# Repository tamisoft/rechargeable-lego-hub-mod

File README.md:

# LEGO HUB-mod, rechargable battery

## Project
The Project was created using KiCAD 5.1.5.
Should be manufactured on a <0.8mm thick PCB (eg. oshpark's 2oz copper service).
The "production" directory has an "interactive bom" to assist with the hand assembly.

## Features
- USB charging at about 400mA
- TI BQ25886, 2A boost charger, optimized for 2S Li-Ion
- NTC
- connector for an 8.4V battery

Recommended battery:
[Soshine 9V 650mAh 6F22](https://lygte-info.dk/review/batteries9V/Soshine%209V%20LiIon%20650mAh%20(White)%20UK.html)

## Finished build
### Board assembled

### USB input

### Charging indicators
- red: charging
- green: power

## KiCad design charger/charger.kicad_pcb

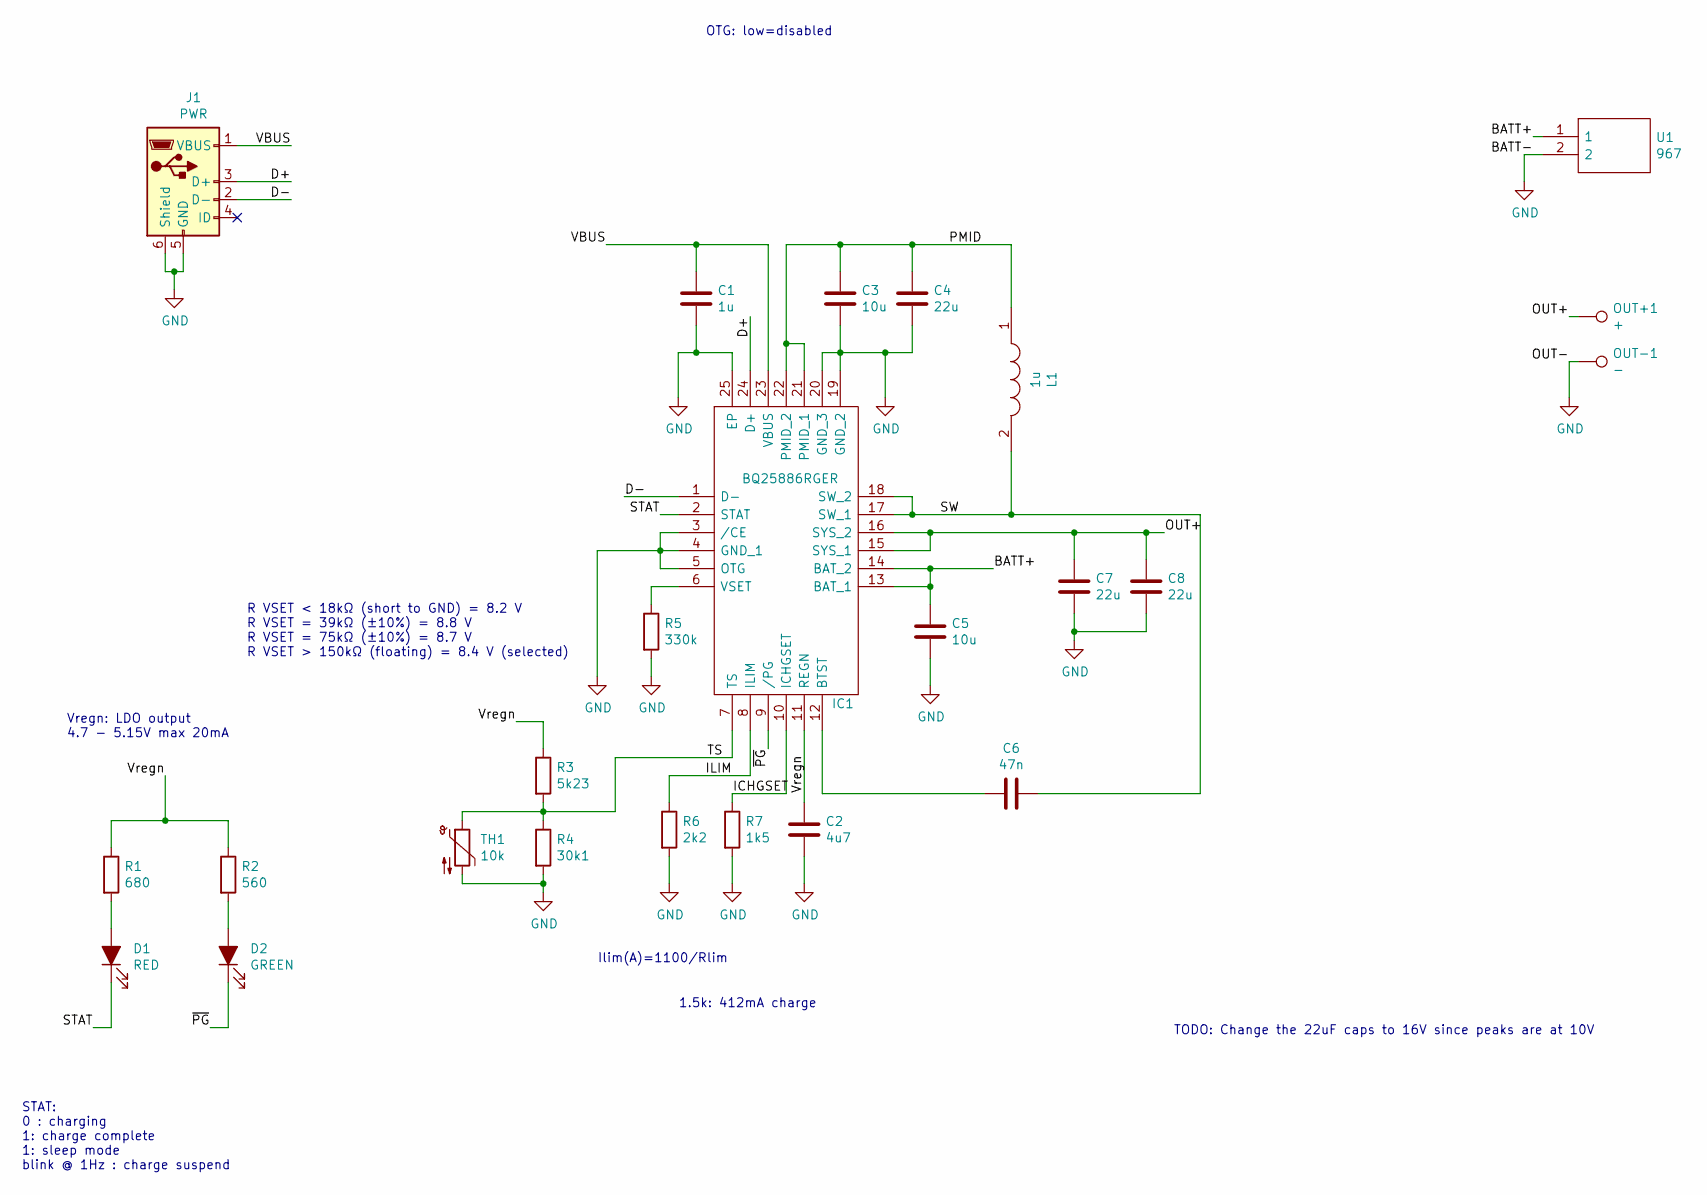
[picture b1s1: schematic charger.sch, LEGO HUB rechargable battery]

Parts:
C1: 1u; C_0603_1608Metric; MOUSER 603-CC603KPX7R7BB105
C2: 4u7; C_0603_1608Metric; MOUSER 963-EMK107ABJ475MA-T
C3, C5: 10u; C_0603_1608Metric; MOUSER 81-GRT188R61C106KE3D
C4, C7, C8: 22u; C_0603_1608Metric; MOUSER 81-ZRB18AR61A226ME1L
C6: 47n; C_0603_1608Metric; MOUSER 603-CC603KPX7R7BB473
D1: RED; HSMAC110; MOUSER 630-HSMH-C110
D2: GREEN; HSMAC110; MOUSER 630-HSMG-C110
IC1: BQ25886RGER; QFN50P400X400X100-25N; Mouser Part Number 595-BQ25886RGER
J1: PWR; USB_Micro-AB_Molex_47590-0001; MOUSER 538-47590-0001
L1: 1u; INDC2520X120N; Mouser Part Number 81-DFE252012F-1R0MP2
OUT+1: +; TestPoint_Pad_1.0x1.0mm
OUT-1: -; TestPoint_Pad_1.0x1.0mm
R1: 680; R_0402_1005Metric; MOUSER 667-ERJ-U02D6800X
R2: 560; R_0402_1005Metric; MOUSER 667-ERJ-2RHD5600X
R3: 5k23; R_0402_1005Metric; MOUSER 603-AC0402FR-075K23L
R4: 30k1; R_0402_1005Metric; MOUSER 667-ERJ-2RHD3012X
R5: 330k; R_0402_1005Metric; MOUSER 71-CRCW0402330KFKEDC
R6: 2k2; R_0402_1005Metric; MOUSER 279-CRGP0402F2K2
R7: 1k5; R_0402_1005Metric; MOUSER 71-CRCW04021K50FKEDC
TH1: 10k; 103AT2; MOUSER 954-103AT-2
U1: 967; Mouser Part Number 534-967

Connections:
/BATT+: C5.1, IC1.13 (BAT_1), IC1.14 (BAT_2), U1.1
/D+: IC1.24 (D+), J1.3 (D+)
/D-: IC1.1 (D-), J1.2 (D-)
/ICHGSET: IC1.10 (ICHGSET), R7.1
/ILIM: IC1.8 (ILIM), R6.1
/OUT+: C7.1, C8.1, IC1.15 (SYS_1), IC1.16 (SYS_2), OUT+1.1
/PMID: C3.1, C4.1, IC1.21 (PMID_1), IC1.22 (PMID_2), L1.1
/STAT: D1.1 (K), IC1.2 (STAT)
/SW: C6.1, IC1.17 (SW_1), IC1.18 (SW_2), L1.2
/TS: IC1.7 (TS), R3.2, R4.1, TH1.1
/VBUS: C1.1, IC1.23 (VBUS), J1.1 (VBUS)
/Vregn: C2.1, IC1.11 (REGN), R1.1, R2.1, R3.1
/~PG: D2.1 (K), IC1.9 (/PG)
GND: C1.2, C2.2, C3.2, C4.2, C5.2, C7.2, C8.2, IC1.3 (/CE), IC1.4 (GND_1), IC1.5 (OTG), IC1.19 (GND_2), IC1.20 (GND_3), IC1.25 (EP), J1.5 (GND), J1.6 (Shield), OUT-1.1, R4.2, R5.2, R6.2, R7.2, TH1.2, U1.2
unnamed: C6.2, IC1.12 (BTST)
unnamed: D1.2 (A), R1.2
unnamed: D2.2 (A), R2.2
unnamed: IC1.6 (VSET), R5.1

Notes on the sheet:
OTG: low=disabled
R VSET < 18kΩ (short to GND) = 8.2 V R VSET = 39kΩ (±10%) = 8.8 V R VSET = 75kΩ (±10%) = 8.7 V R VSET > 150kΩ (floating) = 8.4 V (selected)
STAT: 0 : charging 1: charge complete 1: sleep mode blink @ 1Hz : charge suspend
Vregn: LDO output 4.7 - 5.15V max 20mA
1.5k: 412mA charge
Ilim(A)=1100/Rlim
TODO: Change the 22uF caps to 16V since peaks are at 10V

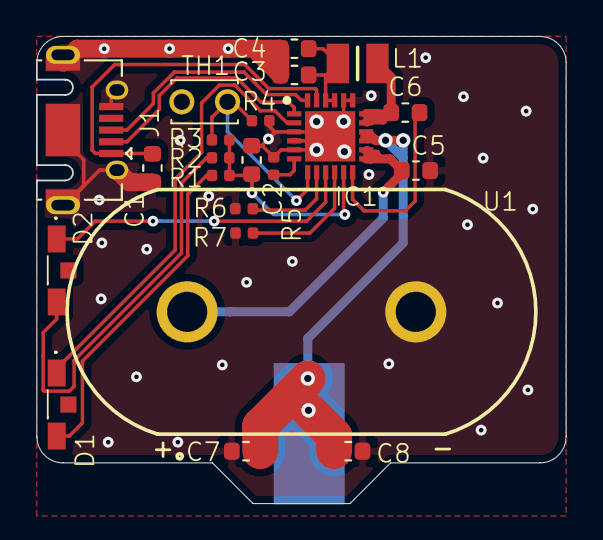
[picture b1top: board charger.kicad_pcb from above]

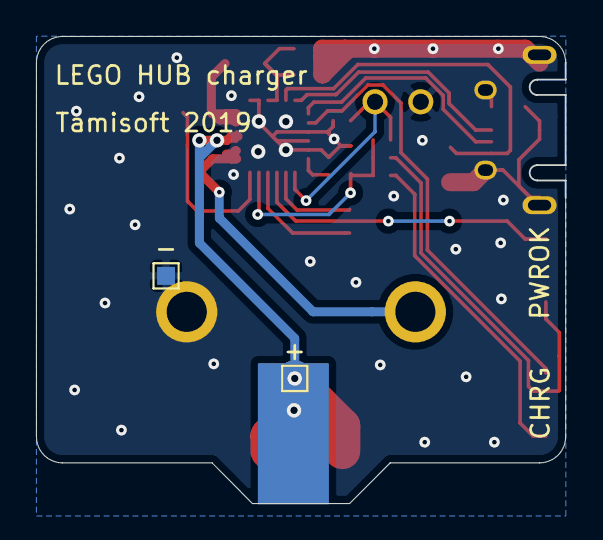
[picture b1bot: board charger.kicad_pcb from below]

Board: 2 copper layers, 29.4 x 25.9 mm, 24 parts (2 on the bottom side), 18 nets.

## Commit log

2020-02-04 HW v1.0.7
    Original repo SHA: e3ecb23773
